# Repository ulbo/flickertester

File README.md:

# flickertester
Using RaspberryPi Pico to visualize flicker of LED lamps

A small project for visualizing the flicker of LED lamps on a display. On the left side the minimum and maximum measured brightness value is shown, on the lower right side the calculated flicker frequency in Hertz.

Implementation is done in MicroPython on a RaspberryPi Pico using a CJMCU breakout board for the OPT101 light sensor and a SH1106 OLED display; both are available in the usual maker shops.

The analogue output value of the OPT101 is digitized by the Pico which shows the waveform on the display. Implementation is quite crude; more a proof-of-concept than a "real" device.

**Circuit**

**Breadboard**

**References**

SH1106 driver: https://github.com/robert-hh/SH1106

OPT101 circuit: https://www.electroschematics.com/photodiode/

DMA code borrowed from https://iosoft.blog/2021/10/26/pico-adc-dma/

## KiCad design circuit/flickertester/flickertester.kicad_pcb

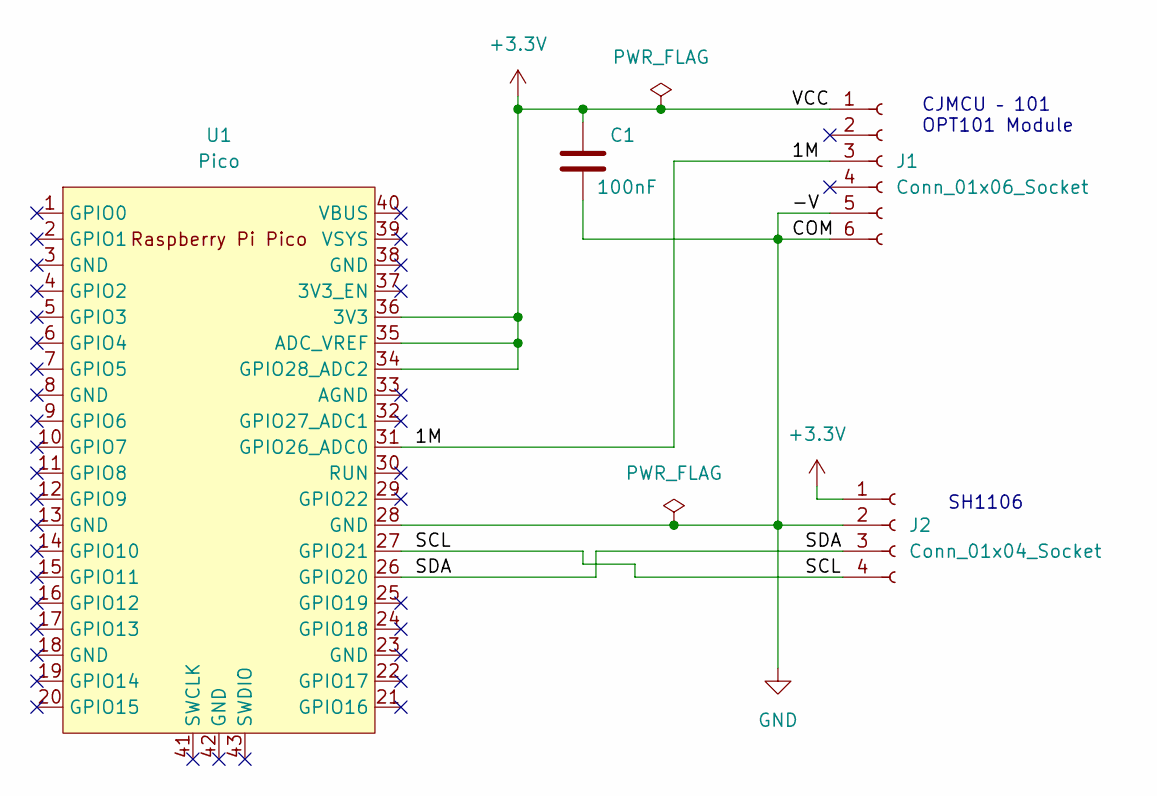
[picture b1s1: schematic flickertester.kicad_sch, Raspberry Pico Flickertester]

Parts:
C1: 100nF; CP_Radial_D5.0mm_P2.50mm
J1: Conn_01x06_Socket; PinSocket_1x06_P2.54mm_Vertical
J2: Conn_01x04_Socket; PinSocket_1x04_P2.54mm_Vertical
U1: Pico; RPi_Pico_SMD_TH

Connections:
+3.3V: C1.1, J1.1, J2.1, U1.34 (GPIO28_ADC2), U1.35 (ADC_VREF), U1.36 (3V3)
/1M: J1.3, U1.31 (GPIO26_ADC0)
/SCL: J2.4, U1.27 (GPIO21)
/SDA: J2.3, U1.26 (GPIO20)
GND: C1.2, J1.5, J1.6, J2.2, U1.28 (GND)

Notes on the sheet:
SH1106
CJMCU – 101 OPT101 Module

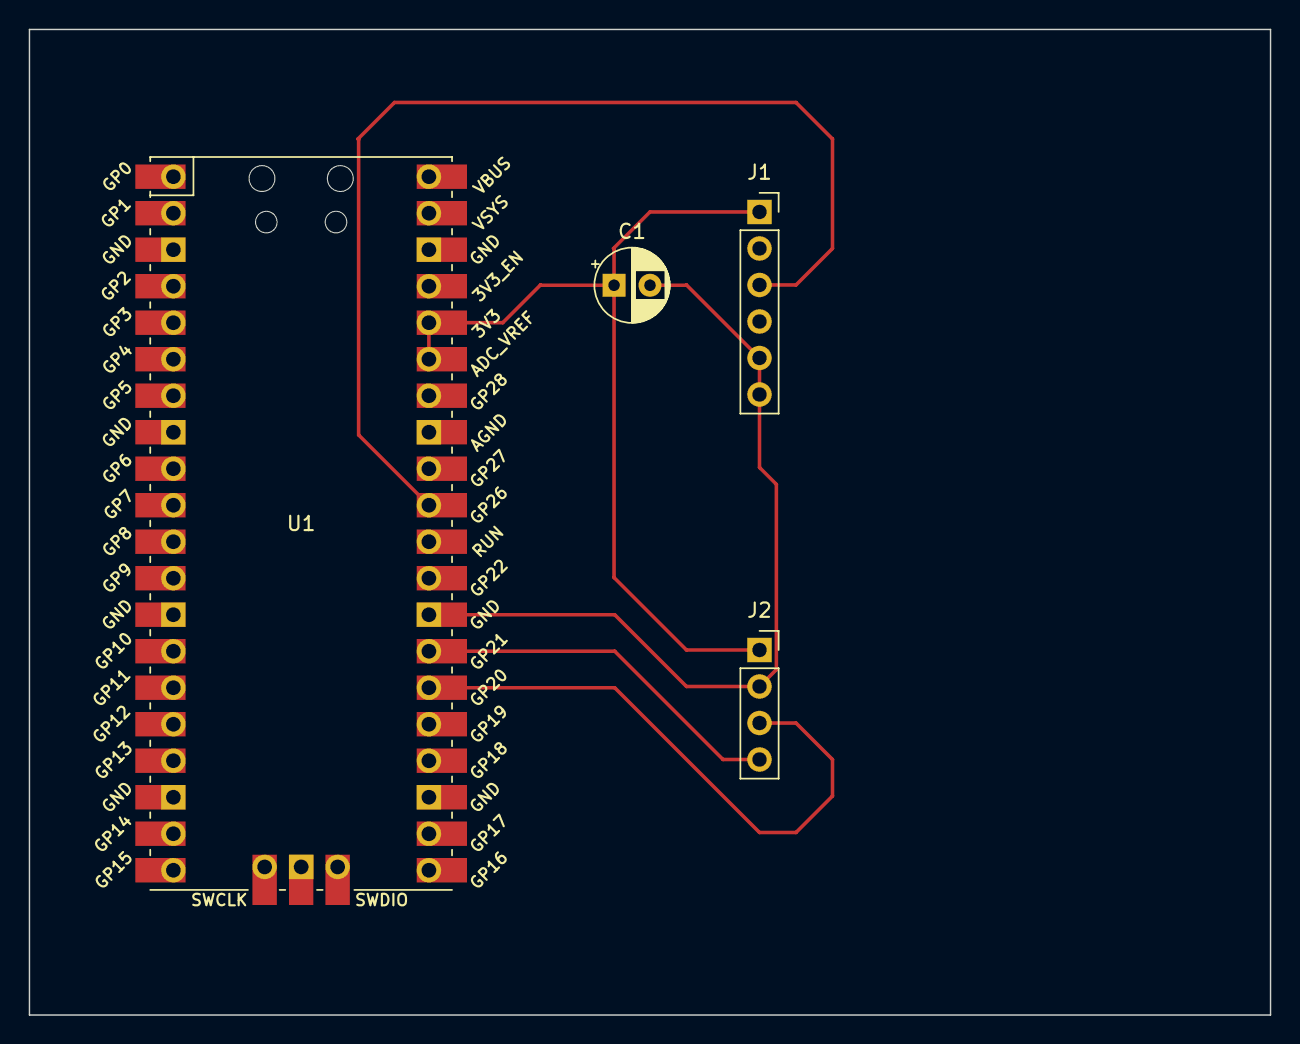
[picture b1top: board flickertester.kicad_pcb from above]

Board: 2 copper layers, 86.4 x 68.6 mm, 4 parts (0 on the bottom side), 5 nets.

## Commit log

2023-11-18 added: source, circuit data and example images
2023-11-21 added example image to README.md
2023-11-21 added breadboard image
2023-11-23 added: circuit image
